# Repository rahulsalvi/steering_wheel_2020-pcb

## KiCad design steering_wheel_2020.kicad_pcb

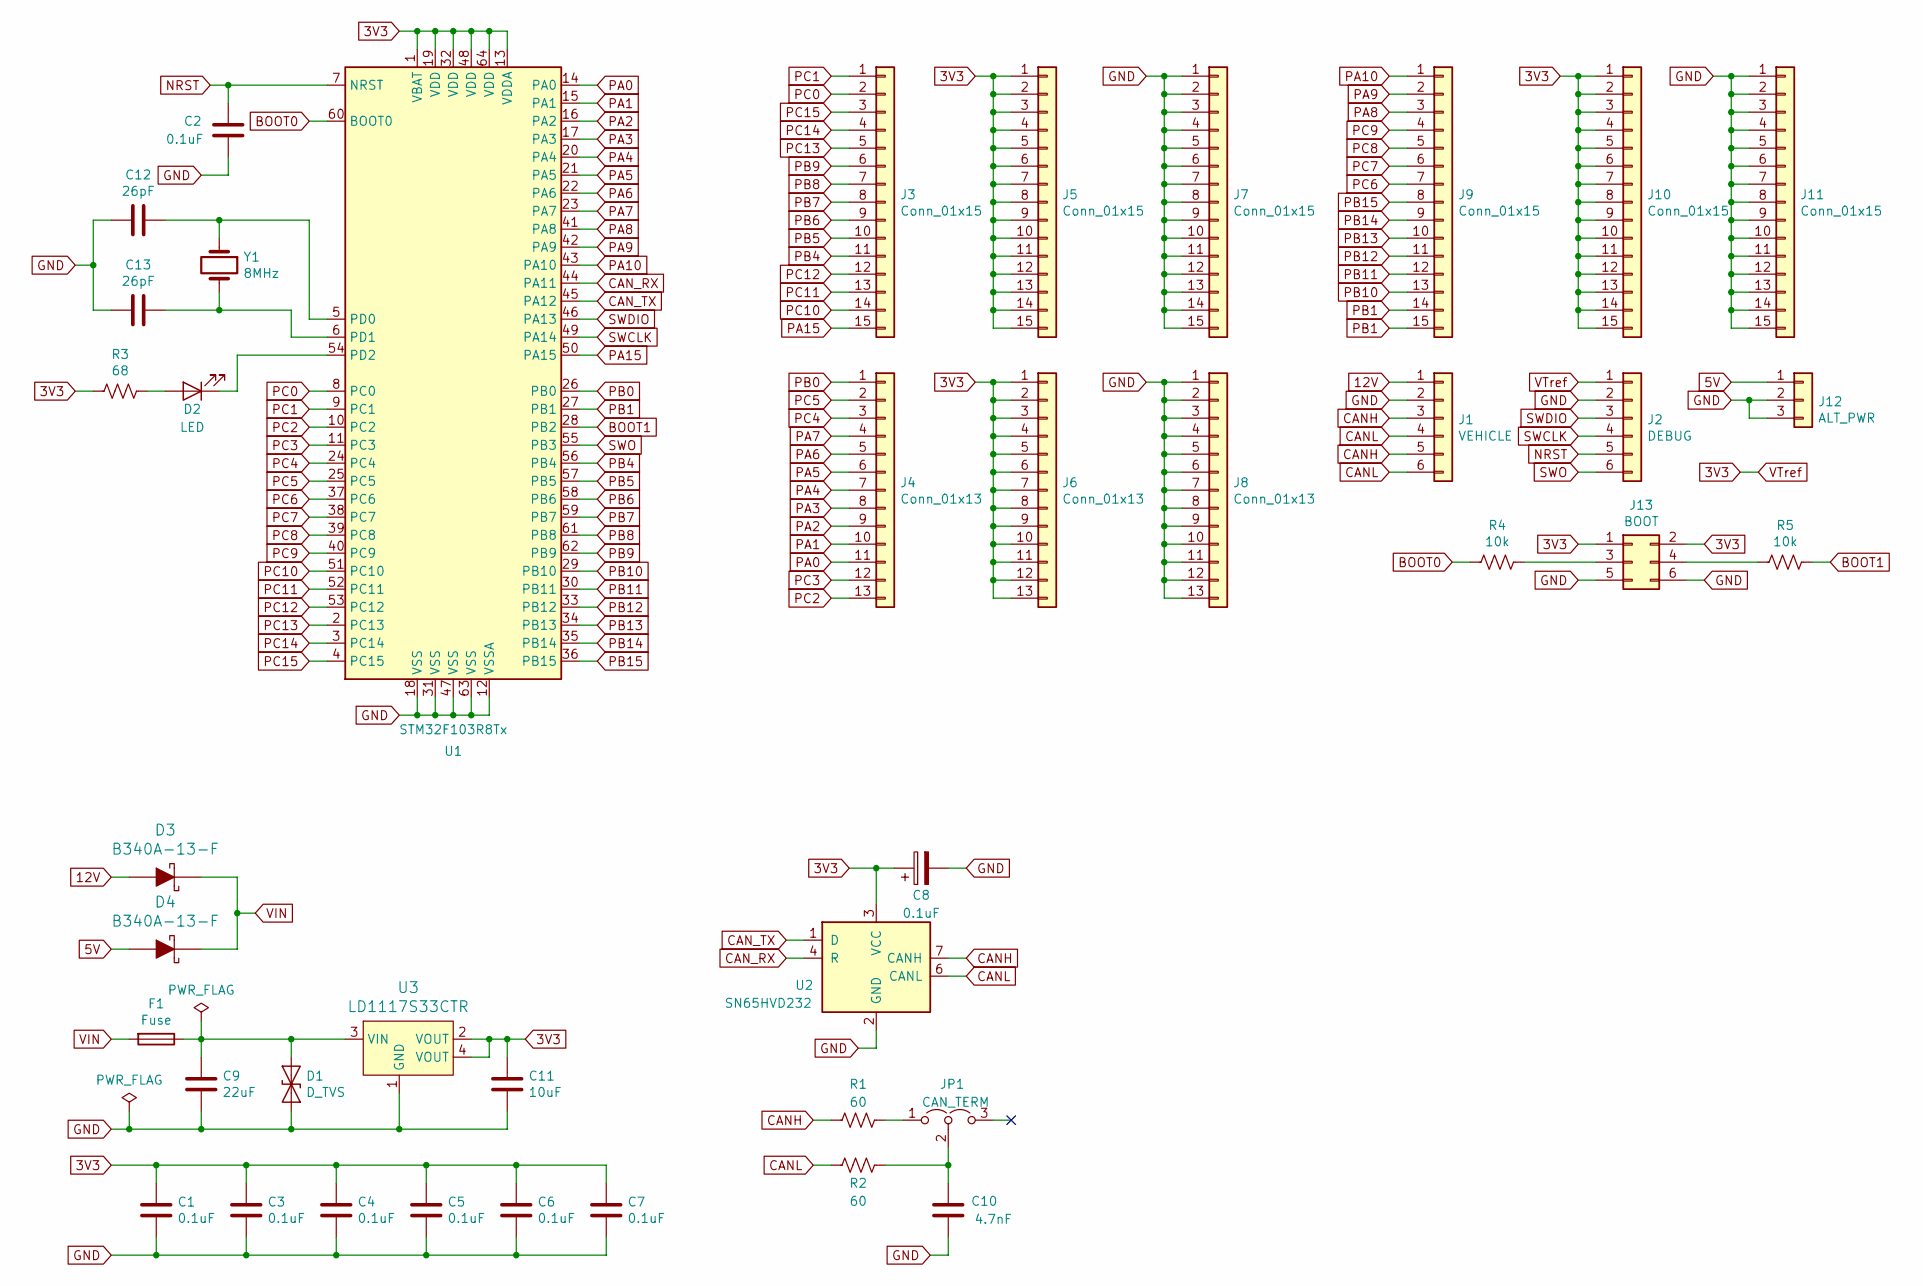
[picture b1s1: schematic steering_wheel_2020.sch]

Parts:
C1, C2, C3, C4, C5, C6, C7, C8: 0.1uF; C_0805_2012Metric_Pad1.15x1.40mm_HandSolder
C9: 22uF; C_0805_2012Metric_Pad1.15x1.40mm_HandSolder
C10: 4.7nF; C_0805_2012Metric_Pad1.15x1.40mm_HandSolder
C11: 10uF; C_0805_2012Metric_Pad1.15x1.40mm_HandSolder
C12, C13: 26pF; C_0805_2012Metric_Pad1.15x1.40mm_HandSolder
D1: D_TVS; DO-214AB_no_polarity
D2: LED; C_0805_2012Metric_Pad1.15x1.40mm_HandSolder
D3, D4: B340A-13-F; DO-214AC; MPN B340A-13-F; Digi-Key_PN B340A-FDICT-ND
F1: Fuse; Fuse_0805_2012Metric_Pad1.15x1.40mm_HandSolder
J1: VEHICLE; PinSocket_1x06_P2.54mm_Vertical
J2: DEBUG; PinSocket_2x03_P2.54mm_Vertical
J3, J5, J7, J9, J10, J11: Conn_01x15; PinSocket_1x15_P2.54mm_Vertical
J4, J6, J8: Conn_01x13; PinSocket_1x13_P2.54mm_Vertical
J12: ALT_PWR; BarrelJack_CUI_PJ-102AH_Horizontal
J13: BOOT; PinHeader_2x03_P2.54mm_Vertical
JP1: CAN_TERM; PinHeader_1x03_P2.54mm_Vertical
R1, R2: 60; R_0805_2012Metric_Pad1.15x1.40mm_HandSolder
R3: 68; R_0805_2012Metric_Pad1.15x1.40mm_HandSolder
R4, R5: 10k; R_0805_2012Metric_Pad1.15x1.40mm_HandSolder
U1: STM32F103R8Tx; LQFP-64_10x10mm_P0.5mm
U2: SN65HVD232; SOIC-8_3.9x4.9mm_P1.27mm
U3: LD1117S33CTR; SOT-223; MPN LD1117S33CTR; Digi-Key_PN 497-1241-1-ND
Y1: 8MHz; Crystal_SMD_TXC_7A-2Pin_5x3.2mm_HandSolder

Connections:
3V3: C1.1, C3.1, C4.1, C5.1, C6.1, C7.1, C8.1, C11.1, J2.1, J5.1, J5.2, J5.3, J5.4, J5.5, J5.6, J5.7, J5.8, J5.9, J5.10, J5.11, J5.12, J5.13, J5.14, J5.15, J6.1, J6.2, J6.3, J6.4, J6.5, J6.6, J6.7, J6.8, J6.9, J6.10, J6.11, J6.12, J6.13, J10.1, J10.2, J10.3, J10.4, J10.5, J10.6, J10.7, J10.8, J10.9, J10.10, J10.11, J10.12, J10.13, J10.14, J10.15, J13.1, J13.2, R3.1, U1.1 (VBAT), U1.13 (VDDA), U1.19 (VDD), U1.32 (VDD), U1.48 (VDD), U1.64 (VDD), U2.3 (VCC), U3.2 (VOUT), U3.4 (VOUT)
5V: D4.A, J12.1
12V: D3.A, J1.1
BOOT0: R4.2, U1.60 (BOOT0)
BOOT1: R5.2, U1.28 (PB2)
CANH: J1.3, J1.5, R1.2, U2.7 (CANH)
CANL: J1.4, J1.6, R2.2, U2.6 (CANL)
CAN_RX: U1.44 (PA11), U2.4 (R)
CAN_TX: U1.45 (PA12), U2.1 (D)
GND: C1.2, C2.2, C3.2, C4.2, C5.2, C6.2, C7.2, C8.2, C9.2, C10.2, C11.2, C12.2, C13.2, D1.2 (A2), J1.2, J2.2, J7.1, J7.2, J7.3, J7.4, J7.5, J7.6, J7.7, J7.8, J7.9, J7.10, J7.11, J7.12, J7.13, J7.14, J7.15, J8.1, J8.2, J8.3, J8.4, J8.5, J8.6, J8.7, J8.8, J8.9, J8.10, J8.11, J8.12, J8.13, J11.1, J11.2, J11.3, J11.4, J11.5, J11.6, J11.7, J11.8, J11.9, J11.10, J11.11, J11.12, J11.13, J11.14, J11.15, J12.2, J12.3, J13.5, J13.6, U1.12 (VSSA), U1.18 (VSS), U1.31 (VSS), U1.47 (VSS), U1.63 (VSS), U2.2 (GND), U3.1 (GND)
NRST: C2.1, J2.5, U1.7 (NRST)
unnamed: C9.1, D1.1 (A1), F1.1, U3.3 (VIN)
unnamed: C10.1, JP1.2 (C), R2.1
unnamed: C12.1, U1.5 (PD0), Y1.1
unnamed: C13.1, U1.6 (PD1), Y1.2
unnamed: D2.1 (K), U1.54 (PD2)
unnamed: D2.2 (A), R3.2
unnamed: J13.3, R4.1
unnamed: J13.4, R5.1
unnamed: JP1.1 (A), R1.1
PA0: J4.11, U1.14 (PA0)
PA1: J4.10, U1.15 (PA1)
PA2: J4.9, U1.16 (PA2)
PA3: J4.8, U1.17 (PA3)
PA4: J4.7, U1.20 (PA4)
PA5: J4.6, U1.21 (PA5)
PA6: J4.5, U1.22 (PA6)
PA7: J4.4, U1.23 (PA7)
PA8: J9.3, U1.41 (PA8)
PA9: J9.2, U1.42 (PA9)
PA10: J9.1, U1.43 (PA10)
PA15: J3.15, U1.50 (PA15)
PB0: J4.1, U1.26 (PB0)
PB1: J9.14, J9.15, U1.27 (PB1)
PB4: J3.11, U1.56 (PB4)
PB5: J3.10, U1.57 (PB5)
PB6: J3.9, U1.58 (PB6)
PB7: J3.8, U1.59 (PB7)
PB8: J3.7, U1.61 (PB8)
PB9: J3.6, U1.62 (PB9)
PB10: J9.13, U1.29 (PB10)
PB11: J9.12, U1.30 (PB11)
PB12: J9.11, U1.33 (PB12)
PB13: J9.10, U1.34 (PB13)
PB14: J9.9, U1.35 (PB14)
PB15: J9.8, U1.36 (PB15)
PC0: J3.2, U1.8 (PC0)
PC1: J3.1, U1.9 (PC1)
PC2: J4.13, U1.10 (PC2)
PC3: J4.12, U1.11 (PC3)
PC4: J4.3, U1.24 (PC4)
PC5: J4.2, U1.25 (PC5)
PC6: J9.7, U1.37 (PC6)
PC7: J9.6, U1.38 (PC7)
PC8: J9.5, U1.39 (PC8)
PC9: J9.4, U1.40 (PC9)
PC10: J3.14, U1.51 (PC10)
PC11: J3.13, U1.52 (PC11)
PC12: J3.12, U1.53 (PC12)
PC13: J3.5, U1.2 (PC13)
PC14: J3.4, U1.3 (PC14)
PC15: J3.3, U1.4 (PC15)
SWCLK: J2.4, U1.49 (PA14)
SWDIO: J2.3, U1.46 (PA13)
SWO: J2.6, U1.55 (PB3)
VIN: D3.K, D4.K, F1.2

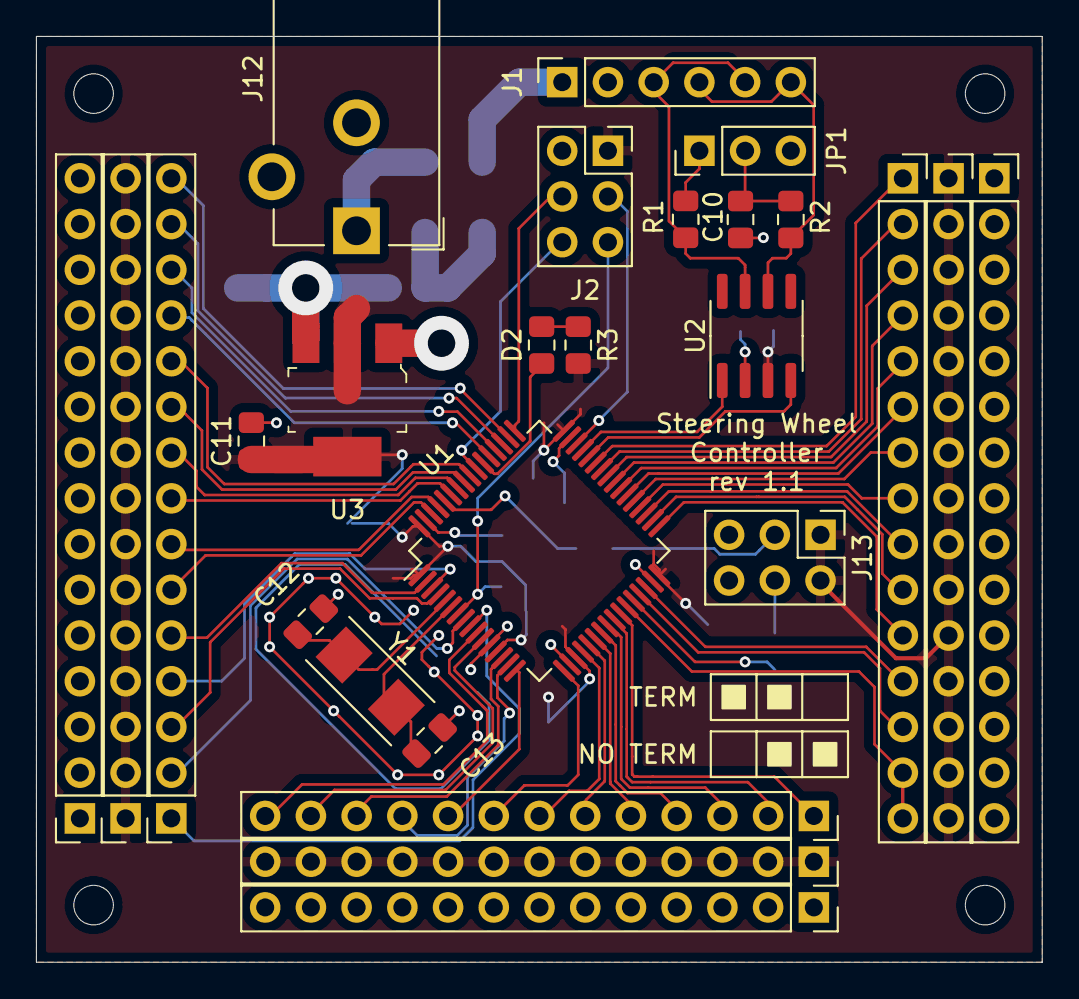
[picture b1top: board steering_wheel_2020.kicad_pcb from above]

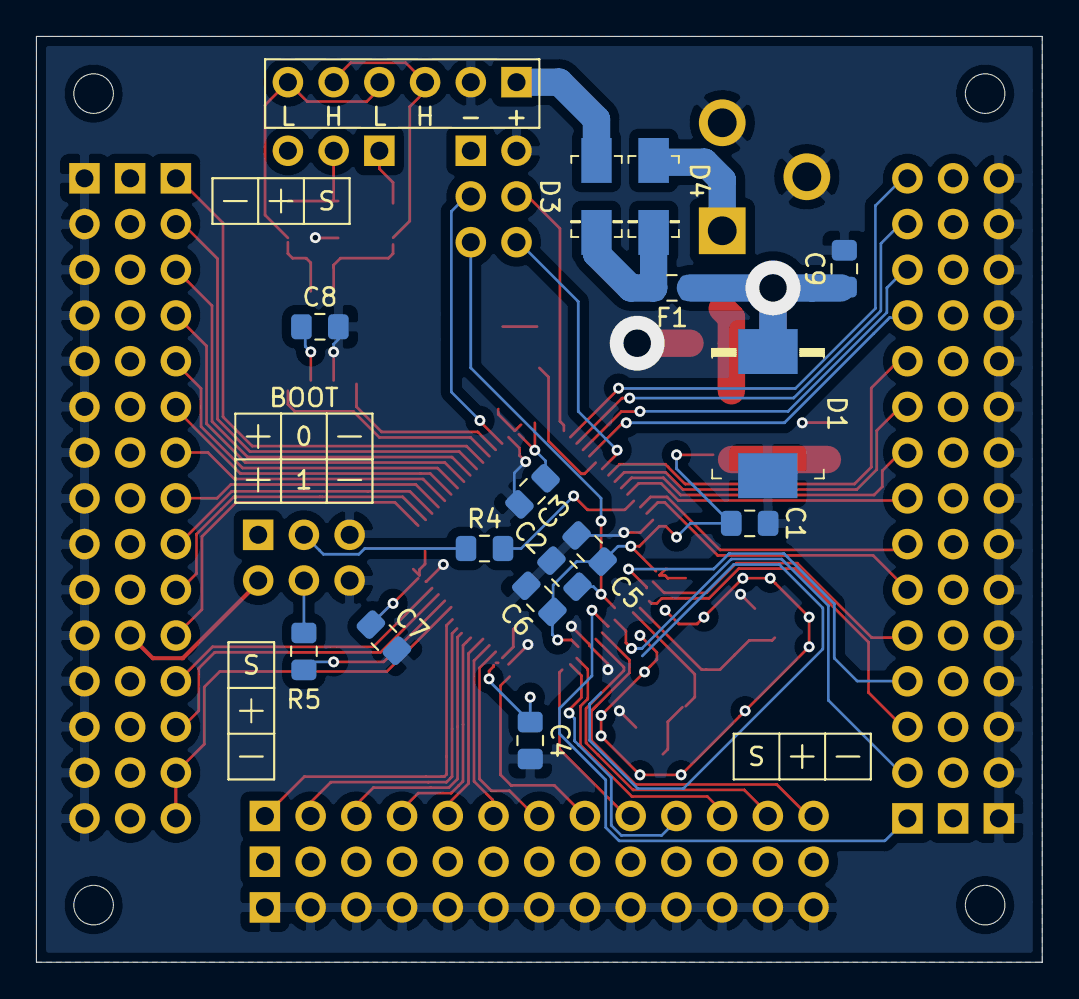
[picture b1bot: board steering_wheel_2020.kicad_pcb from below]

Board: 2 copper layers, 55.9 x 51.4 mm, 41 parts (15 on the bottom side), 66 nets.

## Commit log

2019-10-02 initial
2019-10-05 update gitignore
2019-10-05 add mc and 12v->3.3v circuit
2019-10-05 can transceiver and more mcu connections
2019-10-06 mcu in progress; drc mostly passes
2019-10-09 power circuitry; mcu gpio pins; oscillator
2019-10-09 led indicator
2019-10-09 add output connects
2019-10-11 start layout
2019-10-11 rename files
2019-10-11 add library cache
2019-10-29 begin layout
2019-11-01 routing mostly done
2019-11-01 clean up some traces
2019-11-03 silkscreen done
2019-11-05 solder mask clearance
2020-01-31 Added headers for BOOT0 and BOOT1
2021-01-21 add grid origin
